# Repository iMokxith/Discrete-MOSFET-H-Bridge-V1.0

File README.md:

# Discrete All-N-Channel MOSFET H-Bridge Motor Driver

A complete open-source hardware and software project featuring an **all-N-channel discrete MOSFET H-Bridge motor driver** with bootstrap high-side drivers, designed from scratch without dedicated driver ICs. 

The project includes:
1. **KiCad Hardware Design**: Complete schematic and single-sided PCB layout optimized for DIY home chemical etching (toner transfer method).
2. **Fabrication Files**: 1:1 scale mirrored PDF plot files ready for laser printing on glossy paper.
3. **Arduino Library (`DiscreteHBridge`)**: A plug-and-play Arduino library with built-in bootstrap capacitor protection, dynamic braking, directional dead-time, and smooth acceleration ramping.

demo video

https://github.com/user-attachments/assets/6690fb17-f7f0-4ddb-84b6-009d78a60835

---

## ⚡ Specifications

| Parameter | Specification | Notes |
| :--- | :--- | :--- |
| **Operating Motor Voltage** | 12V – 24V DC | Limited by gate driver ratings & capacitor voltage |
| **Logic Control Voltage** | 5V (Arduino Uno / Nano / Mega) | 3.3V compatible via BC547 base resistors |
| **Control Interface** | 2-Wire Complementary (`IN_A`, `IN_B`) | Only 2 PWM pins required |
| **Power Switches** | 4x N-Channel MOSFETs (IRFZ44N / IRFP150N) | Ultra-low $R_{DS(on)}$ |
| **Gate Driver Stages** | BJT Transistors (11X BC547 NPN + 5X BC557 PNP) | Discrete push-pull stages |
| **Bootstrap Circuit** | 2X 1N4148 diodes + 1X 1000UF(Electrolatic) & 1UF(ceremic) capacitors | High-side gate charge pumping |
| **Flyback Protection** | 4x 1N4007 / Fast Diodes (UF4007 / FR307) | Clamps inductive spikes across motor |
| **PCB Layer** | Single-Layer (`F.Cu` / `B.Cu` compatible) | Optimized 1.5mm clearance for home etching |

---

## 📁 Repository Structure

```text
├── Hardware/                                # KiCad Project Files
│   ├── H_Bridge_motor_driver.kicad_pro      # KiCad project file
│   ├── H_Bridge_motor_driver.kicad_sch      # Complete schematic
│   ├── H_Bridge_motor_driver.kicad_pcb      # Single-layer routed PCB
│   └── Fabrication/                         # Etching transfer sheets
│       ├── H_Bridge_motor_driver-F_Cu.pdf   # 1:1 Mirrored copper layer
│       ├── H_Bridge_motor_driver-Edge_Cuts.pdf # Board outline
│       ├── H_Bridge_motor_driver-F_Silkscreen.pdf # Silkscreen assembly guide
│       └── H_Bridge_motor_driver-F_Silkscreen_Mirrored.pdf # Mirrored for toner transfer
│
├── Arduino_Library/                         # Arduino Driver
│   └── DiscreteHBridge/                     # Installable Arduino library
│       ├── library.properties
│       ├── keywords.txt
│       ├── src/
│       │   ├── DiscreteHBridge.h
│       │   └── DiscreteHBridge.cpp
│       └── examples/
│           ├── BasicMotorTest/
│           └── SerialSpeedControl/
│
├── .gitignore                               # Clean KiCad & build ignore rules
└── README.md
```

---

## 🔌 Hardware Circuit Architecture

### 1. High-Side Bootstrap Push-Pull Drive (Q1 & Q3)
High-side N-channel MOSFETs require their gate voltage to rise **~10V above the motor supply** to turn fully ON. 
- A bootstrap capacitor stores charge from the 12V supply via a 1N4148 diode when the half-bridge output is grounded.
- When the high-side MOSFET turns ON, the bootstrap capacitor floats up with the output, powering a discrete BC547/BC557 push-pull totem pole that rapidly charges and discharges the MOSFET gate capacitance.

### 2. Low-Side Pre-Inverted Push-Pull Drive (Q2 & Q4)
The low-side drivers feature a BC547 pre-inverter stage with a pull-up resistor to +12V. This ensures **Active-High** logic and provides cross-conduction shoot-through protection when paired with the complementary high-side drive.

### 3. Control Truth Table (2-Wire Interface)

| Mode | `IN_A` (Pin 9) | `IN_B` (Pin 10) | Motor State |
| :--- | :--- | :--- | :--- |
| **Dynamic Brake / Stop** | `HIGH` (5V) | `HIGH` (5V) | Both low-sides ON (Grounded) |
| **Forward** | **PWM** (Inverted) | `HIGH` (5V) | Leg B grounded, Leg A pulsed |
| **Reverse** | `HIGH` (5V) | **PWM** (Inverted) | Leg A grounded, Leg B pulsed |

---

## 💻 Arduino Library Usage

### Installation
Copy the `Arduino_Library/DiscreteHBridge` directory into your `Documents/Arduino/libraries/` folder, or zip it and import via **Sketch $\rightarrow$ Include Library $\rightarrow$ Add .ZIP Library**.

### Example Code

```cpp
#include <DiscreteHBridge.h>

// Leg A on Pin 9 (~PWM), Leg B on Pin 10 (~PWM)
DiscreteHBridge motor(9, 10);

void setup() {
  motor.begin(); // Initializes pins and starts in safe Brake mode
}

void loop() {
  // Drive forward at 75% speed
  motor.forward(75);
  delay(3000);

  // Active dynamic brake
  motor.brake();
  delay(1000);

  // Drive reverse at 75% speed
  motor.reverse(75);
  delay(3000);

  // Smoothly ramp down to 0% over 1 second
  motor.rampTo(0, 1000);
  motor.brake();
  delay(2000);
}
```

---

## 🛠️ DIY PCB Fabrication Notes

1. **Printing:** Print `Hardware/Fabrication/H_Bridge_motor_driver-F_Cu.pdf` at **100% scale (no fit to page)** on magazine paper or toner transfer paper using a laser printer.
2. **Transfer:** Iron onto single-sided copper clad board for ~3–5 minutes at high heat.
   
4. **Etching:** Etch in ferric chloride ($FeCl_3$) solution with agitation. The wide 1.5mm ground plane clearance prevents accidental shorts.
5. 

6. **Drilling:** KiCad drill marks are exported with "Small" pilot dimples to prevent drill bit wander when drilling by hand.
7. 

8. **Component Mounting:** All components are mounted on the copper side (`F.Cu`). Ensure 2mm–3mm standoffs on screw terminals and electrolytic capacitors for soldering iron access.
9. 

---

## 📄 License
This project is released under the **MIT License**. Feel free to use, modify, and build upon it for your own projects!

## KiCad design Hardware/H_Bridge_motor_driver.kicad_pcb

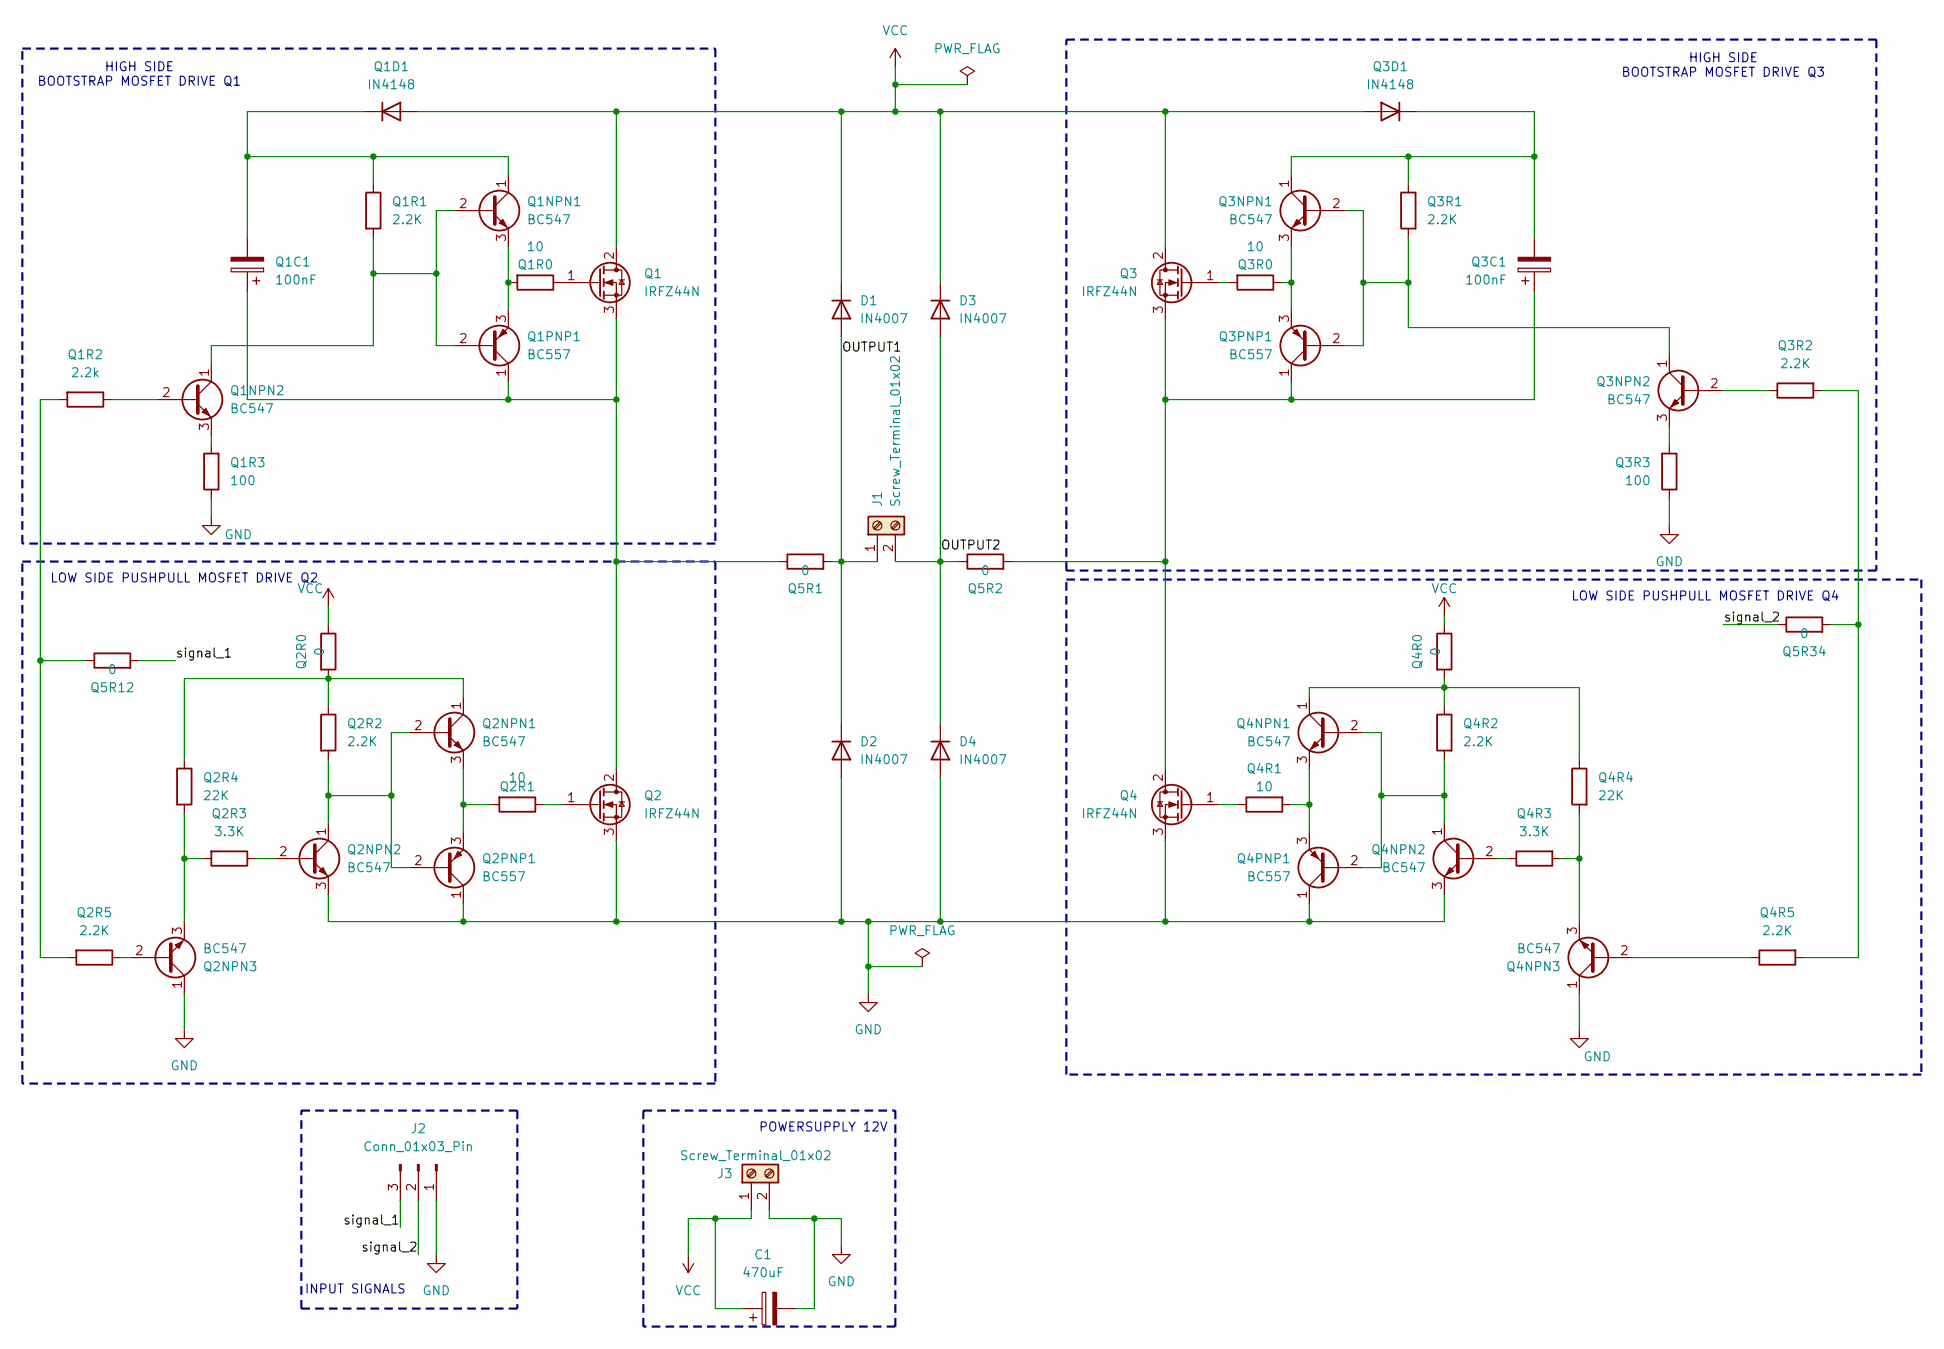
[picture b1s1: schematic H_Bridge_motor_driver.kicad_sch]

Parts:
C1: 470uF; CP_Radial_D10.0mm_P5.00mm
D1, D2, D3, D4: IN4007; D_DO-15_P12.70mm_Horizontal
J1, J3: Screw_Terminal_01x02; TerminalBlock_Phoenix_MKDS-1,5-2_1x02_P5.00mm_Horizontal
J2: Conn_01x03_Pin; PinHeader_1x03_P2.54mm_Vertical
Q1, Q2, Q3, Q4: IRFZ44N; TO-220-3_Vertical
Q1C1, Q3C1: 100nF; CP_Radial_D6.3mm_P2.50mm
Q1D1, Q3D1: IN4148; D_DO-35_SOD27_P7.62mm_Horizontal
Q1NPN1, Q1NPN2, Q2NPN1, Q2NPN2, Q2NPN3, Q3NPN1, Q3NPN2, Q4NPN1, Q4NPN2, Q4NPN3: BC547; TO-92_Inline
Q1PNP1, Q2PNP1, Q3PNP1, Q4PNP1: BC557; TO-92_Inline
Q1R0, Q2R1, Q3R0, Q4R1: 10; R_Axial_DIN0207_L6.3mm_D2.5mm_P7.62mm_Horizontal
Q1R1, Q2R2, Q2R5, Q3R1, Q3R2, Q4R2, Q4R5: 2.2K; R_Axial_DIN0207_L6.3mm_D2.5mm_P7.62mm_Horizontal
Q1R2: 2.2k; R_Axial_DIN0207_L6.3mm_D2.5mm_P7.62mm_Horizontal
Q1R3, Q3R3: 100; R_Axial_DIN0207_L6.3mm_D2.5mm_P7.62mm_Horizontal
Q2R0, Q4R0, Q5R1, Q5R2, Q5R12, Q5R34: 0; R_Axial_DIN0207_L6.3mm_D2.5mm_P7.62mm_Horizontal
Q2R3, Q4R3: 3.3K; R_Axial_DIN0207_L6.3mm_D2.5mm_P7.62mm_Horizontal
Q2R4, Q4R4: 22K; R_Axial_DIN0207_L6.3mm_D2.5mm_P7.62mm_Horizontal

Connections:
/OUTPUT1: D1.2 (A), D2.1 (K), J1.1, Q5R1.2
/OUTPUT2: D3.2 (A), D4.1 (K), J1.2, Q5R2.1
/signal_1: J2.3, Q5R12.2
/signal_2: J2.2, Q5R34.1
GND: C1.2, D2.2 (A), D4.2 (A), J2.1, J3.2, Q1R3.1, Q2.3 (S), Q2NPN2.3 (E), Q2NPN3.1 (C), Q2PNP1.1 (C), Q3R3.1, Q4.3 (S), Q4NPN2.3 (E), Q4NPN3.1 (C), Q4PNP1.1 (C)
unnamed: Q1.1 (G), Q1R0.1
unnamed: Q1.3 (S), Q1C1.1, Q1PNP1.1 (C), Q2.2 (D), Q5R1.1
unnamed: Q1C1.2, Q1D1.1 (K), Q1NPN1.1 (C), Q1R1.1
unnamed: Q1NPN1.2 (B), Q1NPN2.1 (C), Q1PNP1.2 (B), Q1R1.2
unnamed: Q1NPN1.3 (E), Q1PNP1.3 (E), Q1R0.2
unnamed: Q1NPN2.2 (B), Q1R2.1
unnamed: Q1NPN2.3 (E), Q1R3.2
unnamed: Q1R2.2, Q2R5.2, Q5R12.1
unnamed: Q2.1 (G), Q2R1.1
unnamed: Q2NPN1.2 (B), Q2NPN2.1 (C), Q2PNP1.2 (B), Q2R2.2
unnamed: Q2NPN1.1 (C), Q2R0.2, Q2R2.1, Q2R4.1
unnamed: Q2NPN1.3 (E), Q2PNP1.3 (E), Q2R1.2
unnamed: Q2NPN2.2 (B), Q2R3.1
unnamed: Q2NPN3.2 (B), Q2R5.1
unnamed: Q2NPN3.3 (E), Q2R3.2, Q2R4.2
unnamed: Q3.1 (G), Q3R0.2
unnamed: Q3.3 (S), Q3C1.1, Q3PNP1.1 (C), Q4.2 (D), Q5R2.2
unnamed: Q3C1.2, Q3D1.1 (K), Q3NPN1.1 (C), Q3R1.1
unnamed: Q3NPN1.2 (B), Q3NPN2.1 (C), Q3PNP1.2 (B), Q3R1.2
unnamed: Q3NPN1.3 (E), Q3PNP1.3 (E), Q3R0.1
unnamed: Q3NPN2.2 (B), Q3R2.1
unnamed: Q3NPN2.3 (E), Q3R3.2
unnamed: Q3R2.2, Q4R5.2, Q5R34.2
unnamed: Q4.1 (G), Q4R1.1
unnamed: Q4NPN1.2 (B), Q4NPN2.1 (C), Q4PNP1.2 (B), Q4R2.2
unnamed: Q4NPN1.1 (C), Q4R0.2, Q4R2.1, Q4R4.1
unnamed: Q4NPN1.3 (E), Q4PNP1.3 (E), Q4R1.2
unnamed: Q4NPN2.2 (B), Q4R3.1
unnamed: Q4NPN3.2 (B), Q4R5.1
unnamed: Q4NPN3.3 (E), Q4R3.2, Q4R4.2
VCC: C1.1, D1.1 (K), D3.1 (K), J3.1, Q1.2 (D), Q1D1.2 (A), Q2R0.1, Q3.2 (D), Q3D1.2 (A), Q4R0.1

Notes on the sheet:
HIGH SIDE BOOTSTRAP MOSFET DRIVE Q3
LOW SIDE PUSHPULL MOSFET DRIVE Q4
HIGH SIDE BOOTSTRAP MOSFET DRIVE Q1
INPUT SIGNALS
POWERSUPPLY 12V
LOW SIDE PUSHPULL MOSFET DRIVE Q2

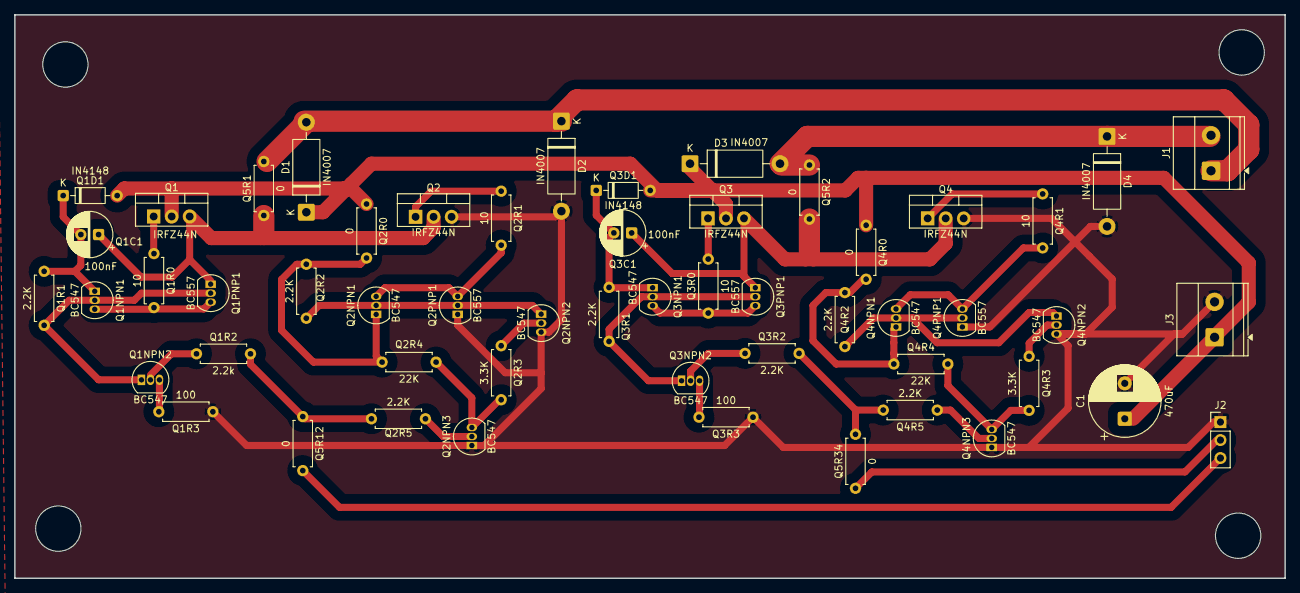
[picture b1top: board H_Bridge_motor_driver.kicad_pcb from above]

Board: 2 copper layers, 179.3 x 79.5 mm, 54 parts (0 on the bottom side), 36 nets.
